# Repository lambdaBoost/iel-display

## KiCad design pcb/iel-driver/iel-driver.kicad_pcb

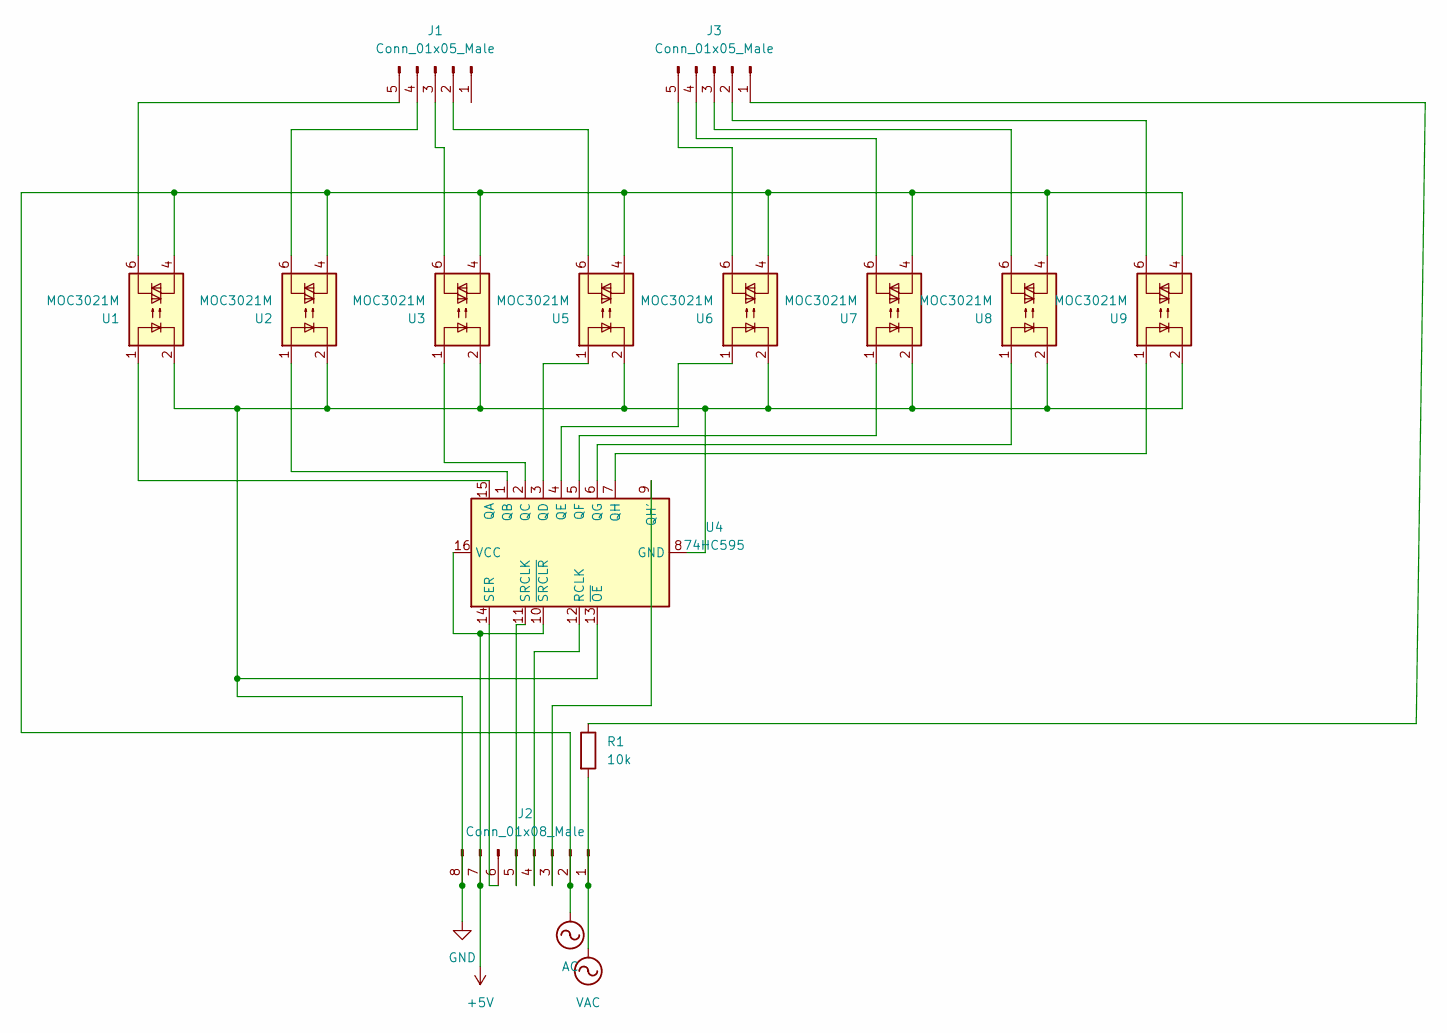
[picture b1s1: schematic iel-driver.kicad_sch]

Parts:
J1: Conn_01x05_Male
J2: Conn_01x08_Male
J3: Conn_01x05_Male; PinHeader_1x05_P2.54mm_Vertical
R1: 10k; R_Axial_DIN0207_L6.3mm_D2.5mm_P15.24mm_Horizontal
U1, U2, U3, U5, U6, U7, U8, U9: MOC3021M; DIP-6_W7.62mm
U4: 74HC595

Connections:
+5V: J2.7, U4.10 (~SRCLR), U4.16 (VCC)
AC: J2.2, U1.4, U2.4, U3.4, U5.4, U6.4, U7.4, U8.4, U9.4
GND: J2.8, U1.2, U2.2, U3.2, U4.8 (GND), U4.13 (~OE), U5.2, U6.2, U7.2, U8.2, U9.2
unnamed: J1.2, U5.6
unnamed: J1.3, U3.6
unnamed: J1.4, U2.6
unnamed: J1.5, U1.6
unnamed: J2.3, U4.9 (QH')
unnamed: J2.4, U4.12 (RCLK)
unnamed: J2.5, U4.11 (SRCLK)
unnamed: J2.6, U4.14 (SER)
unnamed: J3.1, R1.1
unnamed: J3.2, U9.6
unnamed: J3.3, U8.6
unnamed: J3.4, U7.6
unnamed: J3.5, U6.6
unnamed: U1.1, U4.15 (QA)
unnamed: U2.1, U4.1 (QB)
unnamed: U3.1, U4.2 (QC)
unnamed: U4.3 (QD), U5.1
unnamed: U4.4 (QE), U6.1
unnamed: U4.5 (QF), U7.1
unnamed: U4.6 (QG), U8.1
unnamed: U4.7 (QH), U9.1
VAC: J2.1, R1.2

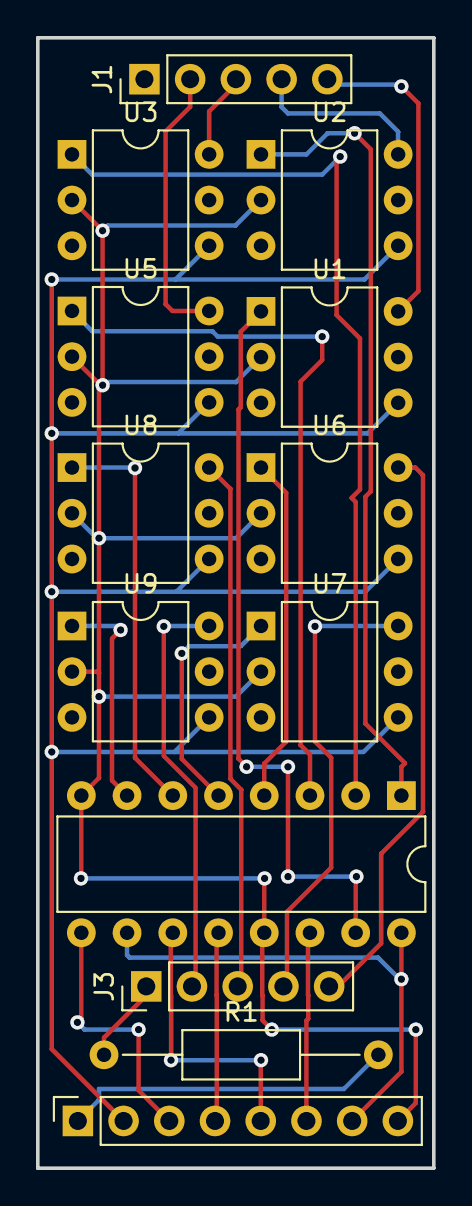
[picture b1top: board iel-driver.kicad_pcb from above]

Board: 2 copper layers, 22.0 x 62.8 mm, 13 parts (0 on the bottom side), 25 nets.

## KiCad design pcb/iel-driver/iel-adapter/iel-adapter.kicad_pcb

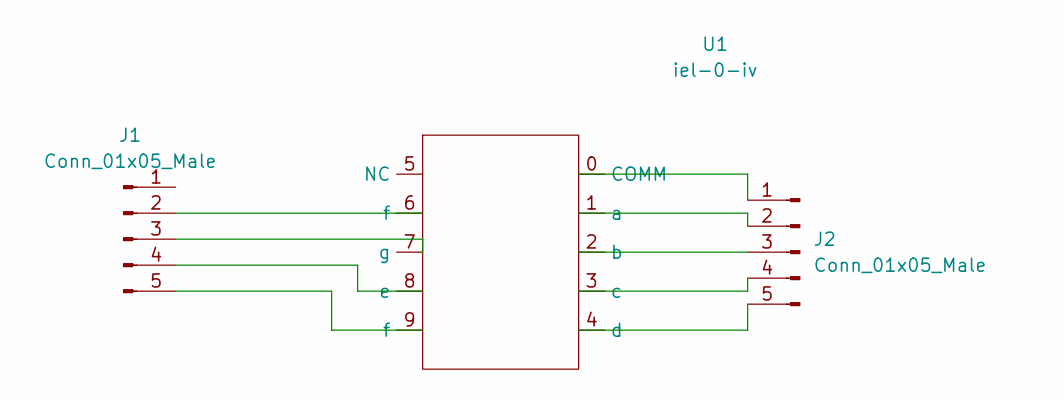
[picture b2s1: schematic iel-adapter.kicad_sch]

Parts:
J1, J2: Conn_01x05_Male; PinHeader_1x05_P2.54mm_Vertical
U1: iel-0-iv

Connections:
unnamed: J1.2, U1.6 (f)
unnamed: J1.3, U1.7 (g)
unnamed: J1.4, U1.8 (e)
unnamed: J1.5, U1.9 (f)
unnamed: J2.1, U1.0 (COMM)
unnamed: J2.2, U1.1 (a)
unnamed: J2.3, U1.2 (b)
unnamed: J2.4, U1.3 (c)
unnamed: J2.5, U1.4 (d)

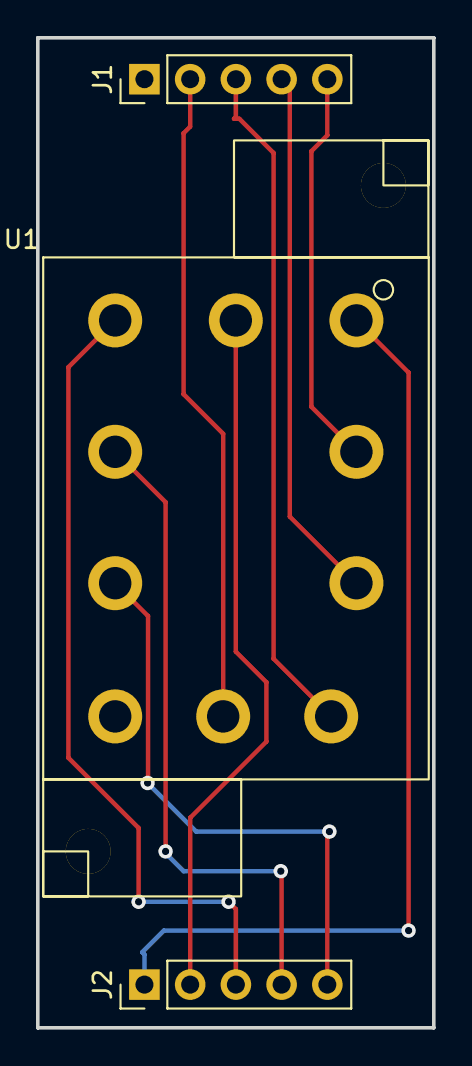
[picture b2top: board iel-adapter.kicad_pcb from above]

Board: 2 copper layers, 22.0 x 55.0 mm, 3 parts (0 on the bottom side), 9 nets.

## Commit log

2022-09-14 added alphanumeric dictionary and display test method
2022-09-18 temporary fix for leading zeros
2022-09-18 typo
2022-10-10 added api get helper function
2022-10-10 added trycatch for connection errors
2023-08-25 replaced main with an actually working script
